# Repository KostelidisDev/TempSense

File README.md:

# TempSense

TempSense is an IoT project based on the NodeSense framework that integrates a temperature sensor.
# License

[MIT License](./LICENSE)

# Disclaimer

This project was conducted as part of the course Ρ101: Embedded Systems in the M.Sc. program in Robotics, offered by the
Department of Computer, Informatics and Telecommunications Engineering at the International Hellenic University.

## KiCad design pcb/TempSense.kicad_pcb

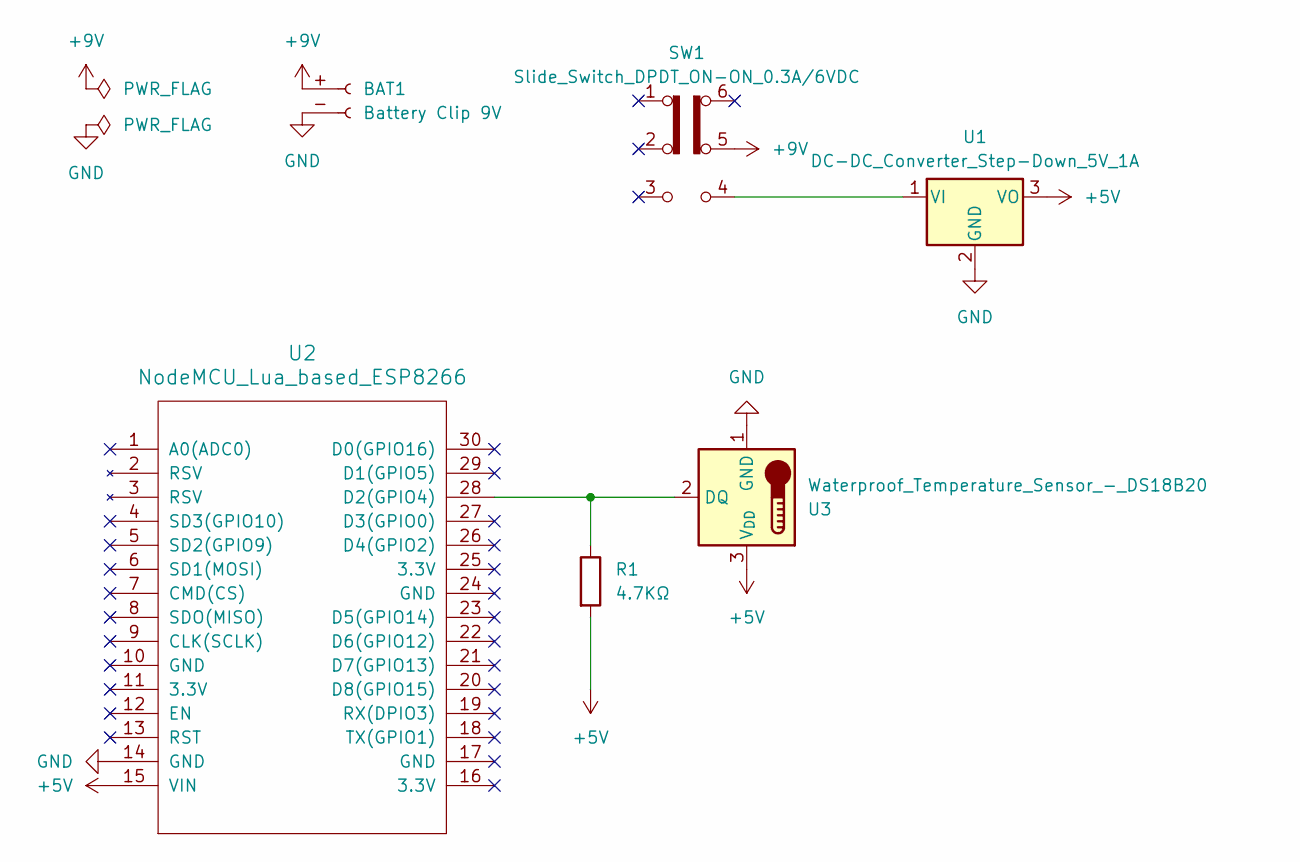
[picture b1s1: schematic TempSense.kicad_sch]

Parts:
BAT1: Battery Clip 9V; Battery_Clip_9V
R1: 4.7ΚΩ; R_Axial_DIN0207_L6.3mm_D2.5mm_P7.62mm_Horizontal
SW1: Slide_Switch_DPDT_ON-ON_0.3A/6VDC; SW_CK_JS202011CQN_DPDT_Straight
U1: DC-DC_Converter_Step-Down_5V_1A; TO-220-3_Vertical
U2: NodeMCU_Lua_based_ESP8266; NodeMCU - Lua based ESP8266
U3: Waterproof_Temperature_Sensor_-_DS18B20

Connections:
+5V: R1.2, U1.3 (VO), U2.15 (VIN), U3.3 (V_{DD})
+9V: BAT1.+ (Pin_1), SW1.5 (B)
GND: BAT1.- (Pin_2), U1.2 (GND), U2.14 (GND), U3.1 (GND)
unnamed: SW1.4 (A), U1.1 (VI)
unnamed: R1.1, U2.28 (D2(GPIO4)), U3.2 (DQ)

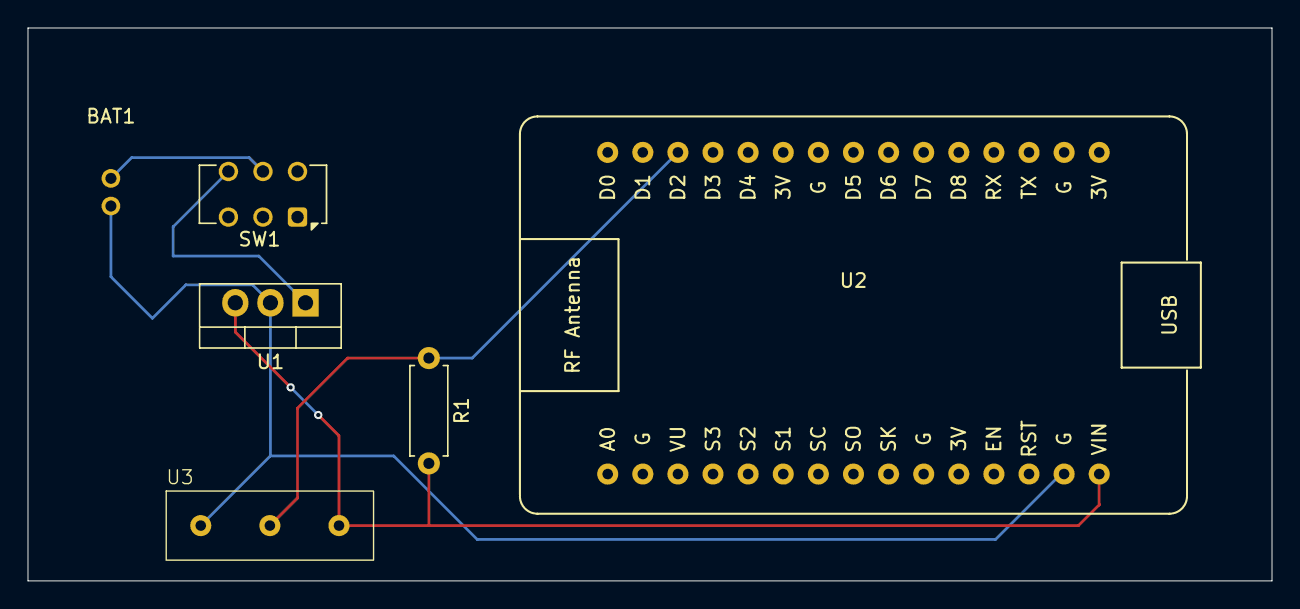
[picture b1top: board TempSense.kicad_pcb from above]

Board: 2 copper layers, 90.0 x 40.0 mm, 6 parts (0 on the bottom side), 5 nets.

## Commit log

2024-12-22 add dependencies
2024-12-22 update env variables
2024-12-22 fix one wire bus env variable parsing
2024-12-22 add support for temp sensor
2024-12-23 Remove .DS_Store files and ignore them
2024-12-23 Remove WIFI credentials from logs
2024-12-23 refactor and add platform info and more logs
2025-01-06 add KiCad project (schematic and pcb)
2025-01-15 resistor connection corrected to 5V
2025-01-31 update schematic
